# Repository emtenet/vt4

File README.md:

# vt4

Video terminal in the style of [VT100](https://en.wikipedia.org/wiki/VT100)
to monitor four computers via their RS-232 consoles.

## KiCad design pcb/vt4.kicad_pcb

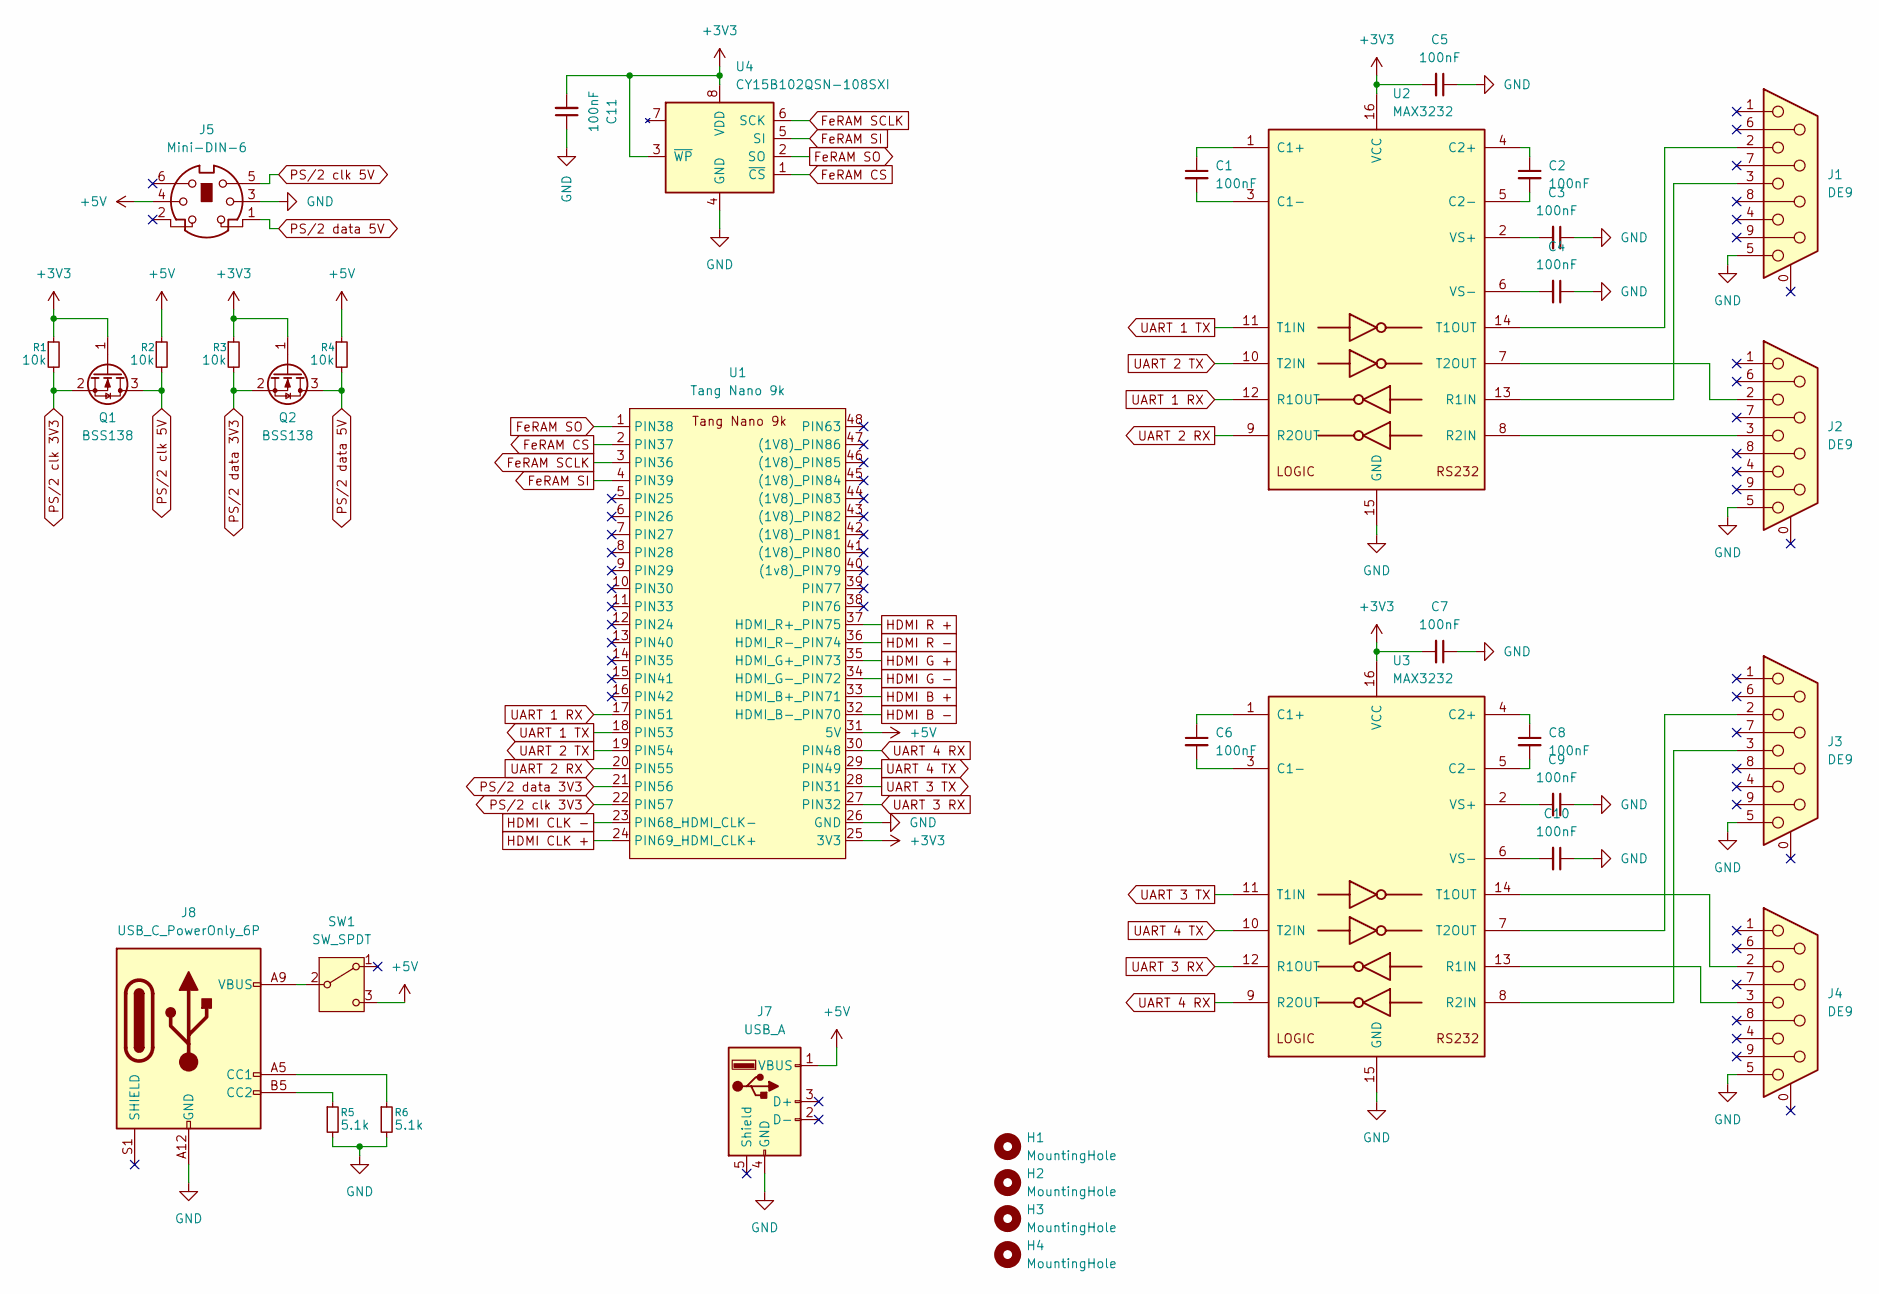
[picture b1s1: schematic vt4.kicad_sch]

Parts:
C1, C2, C3, C4, C5, C6, C7, C8, C9, C10, C11: 100nF; C_1206_3216Metric_Pad1.33x1.80mm_HandSolder
H1, H2, H3, H4: MountingHole; MountingHole_3.2mm_M3
J1, J2, J3, J4: DE9; DSUB_9_Pins_Female_Horizontal
J5: Mini-DIN-6; Mini_DIN_round_6_canned
J7: USB_A; USB_A_Stewart_SS-52100-001_Horizontal
J8: USB_C_PowerOnly_6P; USB_C_Receptacle_GCT_USB4125-xx-x-0190_6P_TopMnt_Horizontal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
Q1, Q2: BSS138; SOT-23_Handsoldering
R1, R2, R3, R4: 10k; R_1206_3216Metric_Pad1.30x1.75mm_HandSolder
R5, R6: 5.1k; R_1206_3216Metric_Pad1.30x1.75mm_HandSolder
SW1: SW_SPDT; SW_Lever_1P2T_NKK_GW12LxH
U1: Tang Nano 9k
U2, U3: MAX3232; SOIC-16_3.9x9.9mm_P1.27mm_Handsolder
U4: CY15B102QSN-108SXI; SOIC-8_5.3x5.3mm_P1.27mm_Handsolder

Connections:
+3V3: C5.2, C7.2, C11.2, Q1.1 (G), Q2.1 (G), R1.1, R3.1, U1.25 (3V3), U2.16 (VCC), U3.16 (VCC), U4.3 (~WP), U4.8 (VDD)
+5V: J5.4, J7.1 (VBUS), R2.1, R4.1, SW1.3 (C), U1.31 (5V)
FeRAM CS: U1.2 (PIN37), U4.1 (~CS)
FeRAM SCLK: U1.3 (PIN36), U4.6 (SCK)
FeRAM SI: U1.4 (PIN39), U4.5 (SI)
FeRAM SO: U1.1 (PIN38), U4.2 (SO)
GND: C3.1, C4.1, C5.1, C7.1, C9.1, C10.1, C11.1, J1.5, J2.5, J3.5, J4.5, J5.3, J7.4 (GND), J8.A12 (GND), J8.B12 (GND), R5.2, R6.2, U1.26 (GND), U2.15 (GND), U3.15 (GND), U4.4 (GND)
HDMI B +: U1.33 (HDMI_B+_PIN71)
HDMI B -: U1.32 (HDMI_B-_PIN70)
HDMI CLK +: U1.24 (PIN69_HDMI_CLK+)
HDMI CLK -: U1.23 (PIN68_HDMI_CLK-)
HDMI G +: U1.35 (HDMI_G+_PIN73)
HDMI G -: U1.34 (HDMI_G-_PIN72)
HDMI R +: U1.37 (HDMI_R+_PIN75)
HDMI R -: U1.36 (HDMI_R-_PIN74)
unnamed: J8.A5 (CC1), R6.1
unnamed: J8.B5 (CC2), R5.1
unnamed: J8.A9 (VBUS), J8.B9 (VBUS), SW1.2 (B)
unnamed: C1.1, U2.1 (C1+)
unnamed: C1.2, U2.3 (C1-)
unnamed: C2.1, U2.4 (C2+)
unnamed: C2.2, U2.5 (C2-)
unnamed: J1.3, U2.13 (R1IN)
unnamed: J2.3, U2.8 (R2IN)
unnamed: J1.2, U2.14 (T1OUT)
unnamed: J2.2, U2.7 (T2OUT)
unnamed: C3.2, U2.2 (VS+)
unnamed: C4.2, U2.6 (VS-)
unnamed: C6.1, U3.1 (C1+)
unnamed: C6.2, U3.3 (C1-)
unnamed: C8.1, U3.4 (C2+)
unnamed: C8.2, U3.5 (C2-)
unnamed: J4.3, U3.13 (R1IN)
unnamed: J3.3, U3.8 (R2IN)
unnamed: J4.2, U3.14 (T1OUT)
unnamed: J3.2, U3.7 (T2OUT)
unnamed: C9.2, U3.2 (VS+)
unnamed: C10.2, U3.6 (VS-)
PS/2 clk 3V3: Q1.2 (S), R1.2, U1.22 (PIN57)
PS/2 clk 5V: J5.5, Q1.3 (D), R2.2
PS/2 data 3V3: Q2.2 (S), R3.2, U1.21 (PIN56)
PS/2 data 5V: J5.1, Q2.3 (D), R4.2
UART 1 RX: U1.17 (PIN51), U2.12 (R1OUT)
UART 1 TX: U1.18 (PIN53), U2.11 (T1IN)
UART 2 RX: U1.20 (PIN55), U2.9 (R2OUT)
UART 2 TX: U1.19 (PIN54), U2.10 (T2IN)
UART 3 RX: U1.27 (PIN32), U3.12 (R1OUT)
UART 3 TX: U1.28 (PIN31), U3.11 (T1IN)
UART 4 RX: U1.30 (PIN48), U3.9 (R2OUT)
UART 4 TX: U1.29 (PIN49), U3.10 (T2IN)

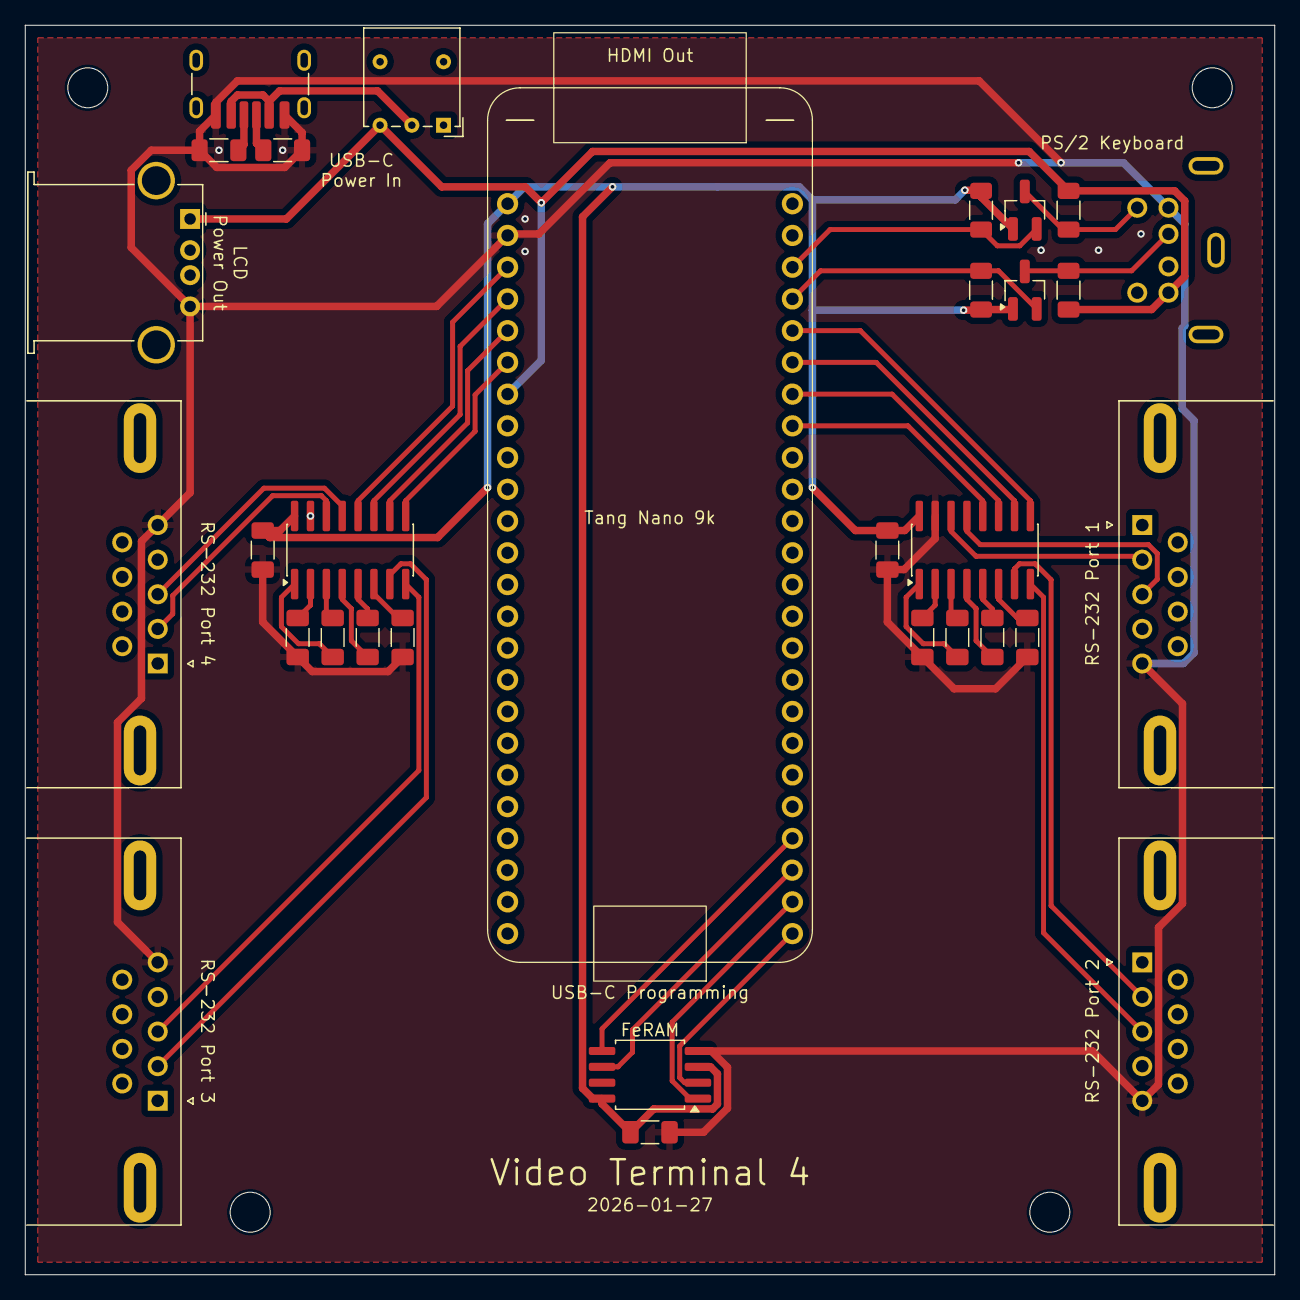
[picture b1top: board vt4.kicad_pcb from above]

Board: 2 copper layers, 100.0 x 100.0 mm, 35 parts (0 on the bottom side), 42 nets.

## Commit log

2025-11-15 Start README.md
2025-11-15 Update README.md
    Spelling
2025-11-16 Start `char-rom-gen` utility
    Initial rust project to generate a Verilog character ROM from a bitmap font
2025-11-16 First draft of char-rom-gen implementation
2025-11-18 Got the Yosys toolchain working in WSL
    Leave bare minimum breadcrumbs of how I did it
    Add a Windows script to run before running `openFPGALoader` inside WLS.
2025-11-18 Bare bones Tang Nano 9x project with 5-inch 800x480 LCD
2025-11-18 Use char_rom to show watermark on LCD
2025-11-19 Display the whole char_rom on the LCD
2025-11-20 Add glyphs for control characters (ASCII 1..31)
2025-11-23 Add images for backlight documentation
2025-11-23 Add documentation to enable/disable the LCD backlight
2025-11-23 Highlight R24 on PCB
2025-11-23 Test the LCD backlight enable/disable wiring after R24 has been shorted
2025-11-23 Revise char-rom glyphs
    Construct "^C" style control codes (1..31)
    Construct diagonal two digit hex glyphs for non-ASCII
2025-11-23 Add VRAM and some refactoring
    Generate some VRAM with interesting initial content
    Refactor VGA to refer to row/col instead of v/h
    Provide registered is_first/is_start directly from vga_axis
2025-12-28 A bit of clean up before replacing LCD with HDMI
2025-12-28 Output HDMI for a 10.1 inch 1024 x 600 panel
2025-12-30 Refactor HDMI pipeline into its own module
2025-12-30 Replace assign statements with always @(#)
2025-12-30 Rename to top.cst
2025-12-30 Remove some Verilog warnings
2025-12-30 Use a clock synchronizer on the PLL `lock` to produce the `reset_low` signal
2025-12-30 Add a PS/2 receiver
    Show low 6 bits of PS/2 data bytes on LED
2025-12-30 Increase debouncer cycles
2025-12-30 Show PS/2 bytes on HDMI display
2025-12-30 Convert VRAM to use ready/valid handshakes
2026-01-01 Show PS/2 errors on LED
2026-01-02 Refactor PS/2 module
    * Rename port interface to scan_code/_ready/_valid
    * Refactor state/frame state loop
    * Add a watchdog timer (now hot plug of keyboard works)
2026-01-02 Make verilator's lint happy
2026-01-02 Buggy PS/2 module pending a verilator test bench
2026-01-02 Move all Verilog files into `src` folder to make verliator usage easier
2026-01-02 Missed previous source shuffle
2026-01-03 Add PS/2 "self test" test
2026-01-03 Refactor PS/2 test so that a second test can share code
2026-01-03 Add failing PS/2 test for sending a RESET command
2026-01-03 PS/2 tests pass and can reliably send a RESET command
2026-01-04 Standard reset_low & diagnosis[] to watch boot timings
2026-01-04 Add PS/2 command ACK channel (with error bit)
2026-01-04 Split out character_writer module
2026-01-04 Refactor top module to read as a pipeline from top to bottom
2026-01-04 A little refactor
2026-01-04 Switch to SystemVerilog
2026-01-04 Forgot in switch to SystemVerilog
2026-01-04 Move common localparam(s) into a package
2026-01-05 Clean up some verilator lints
2026-01-06 CAPS LOCK & NUM LOCK now work! They toggle the LEDs!
2026-01-07 First draft of a scan code to key code lookup table
2026-01-07 Set LEDs after PS/2 self test
2026-01-07 At least key_code.sv parses
2026-01-08 Rename ps2 & keyboard modules to ps2_protocol & ps2_state inside a new ps2 module
2026-01-08 Put PS/2 pin in/out/oe & debouncing into ps2_physical module
2026-01-08 Separate out PS/2 command sending logic into ps2_commands module
2026-01-08 Convert PS/2 scan codes to key codes
2026-01-09 Add uart modules with tests
2026-01-09 PS/2 and UART tests share common simulation_base.h
2026-01-09 Connect up UART to PS/2 and HDMI uart RX -> HDMI PS/2 -> uart TX
2026-01-12 Fix bug where characters where displayed once column to the right. Remove REG on stage2_byte which was registering the previous character.
2026-01-12 Use always_ff, always_comb and begin/end
2026-01-12 Connect UART pins to external MAX3232 chip instead of the one tunnelled through the USB programming header
2026-01-12 Start work towards Video Terminal (vt) logic in vt.sv * rename from character_writer * add cursor_row/col to highlight on display * scroll top_row when at the bottom_row
2026-01-12 Process control codes BS, CR & LF and implement (clear) scrolling
2026-01-14 First draft of PCB
2026-01-14 Add name and order pcb
2026-01-14 PCB fail - connected UART 1 up to HDMI clk pins
2026-01-23 Update pins (and use UART #4) to test on PCB
2026-01-23 Update PCB based on what was learnt soldering & testing
2026-01-26 Send PCB of for manufacturing * switch FeRAM to 3V3 pins (and supply) * update FPGA pin numbers to match
2026-02-13 Test out a coloured border as a way of indicating the active UART 1..4
2026-02-13 Fix up pins for UART 3 & 4
2026-02-21 Still got issues after improving the soldering
2026-02-22 Rename bytes from hosts to be displayed as `display_code`
2026-02-22 Set up for loop back test between ports 3 & 4
2026-02-22 Start documenting PS/2 modules
2026-02-22 Renaming as a form of documentation
2026-02-28 Fix naming
2026-03-01 Move UART module into VT module
2026-03-01 Move VRAM into VT
2026-03-01 Instantiate four (4) VT(s)
2026-03-01 Switch between the 4 ports with Alt-F1 .. Alt-F4
2026-03-01 Multiplex active VT port to HDMI display
